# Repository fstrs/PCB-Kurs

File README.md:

# FHDO-PCB

Felix Strauß

Repository for FH Dortmund - Choiceduty-Module 4th Semster

We will design our own Bluetooth Speaker

- `/Code` -> Programmierungsdateien  
- `/Datenblätter` -> Datenblätter für Verwendete ICs und andere Komponenten  
- `/Dokumentation` -> Vorträge, Dokumentation der Projektarbeit  
- `/PCB` -> Dateien zum PCB-Design  

The full Documentation of the Project can be found at [Ausarbeitung.pdf](https://github.com/fstrs/PCB-Kurs/blob/main/Dokumentation/Ausarbeitung.pdf "Dokumentation/Ausarbeitung.pdf")

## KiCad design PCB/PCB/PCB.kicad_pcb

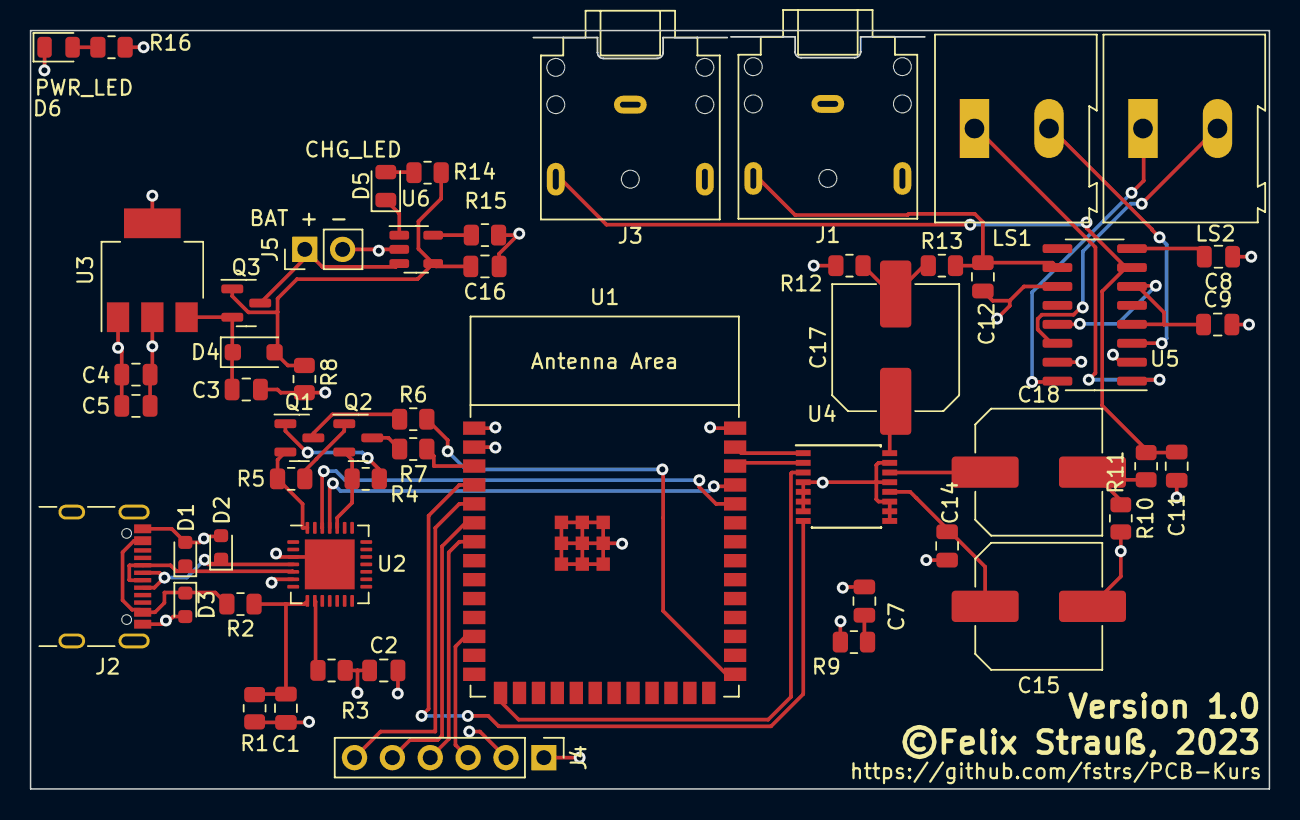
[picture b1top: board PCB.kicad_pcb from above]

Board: 4 copper layers, 83.1 x 50.8 mm, 53 parts (0 on the bottom side), 46 nets.

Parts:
C1, C5: 1u; C_0805_2012Metric
C2, C3, C4: 10u; C_0805_2012Metric
C7, C9, C16: 10µF; C_0805_2012Metric
C8, C14: 100nF; C_0805_2012Metric
C11, C12: 10nF; C_0805_2012Metric
C15, C17, C18: 47µF; C_Elec_8x10.2
D1, D2, D3: D_TVS; D_0603_1608Metric
D4: SS34FA; D_SOD-123F
D5: CHG_LED; LED_0805_2012Metric
D6: PWR_LED; LED_0805_2012Metric
J1: AudioJack Right; Jack_3.5mm_CUI_SJ1-3523N_Horizontal
J2: USB_C_Receptacle_USB2.0; USB_C_Receptacle_GCT_USB4105-xx-A_16P_TopMnt_Horizontal
J3: AudioJack Left; Jack_3.5mm_CUI_SJ1-3523N_Horizontal
J4: 6PIN DISPLAY CONNECTOR; PinHeader_1x06_P2.54mm_Vertical
J5: CONN BAT; PinHeader_1x02_P2.54mm_Vertical
LS1: Speaker Left; TerminalBlock_Altech_AK300-2_P5.00mm
LS2: Speaker Right; TerminalBlock_Altech_AK300-2_P5.00mm
Q1, Q2: BC817; SOT-23
Q3: BSS84; SOT-23
R1: 47K; R_0805_2012Metric
R2: 22K; R_0805_2012Metric
R3, R6, R7: 1K; R_0805_2012Metric
R4, R5, R8, R16: 10K; R_0805_2012Metric
R9: 1; R_0805_2012Metric
R10, R12: 220; R_0805_2012Metric
R11, R13: 100; R_0805_2012Metric
R14: 470; R_0805_2012Metric
R15: 2K; R_0805_2012Metric
U1: ESP32-S3-WROOM-1
U2: CP2102N-Axx-xQFN28; QFN-28-1EP_5x5mm_P0.5mm_EP3.35x3.35mm
U3: NCP1117-3.3_SOT223; SOT-223-3_TabPin2
U4: UDA1334ATS; SSOP-16_4.4x5.2mm_P0.65mm
U5: PAM8403D; SOP-16_3.9x9.9mm_P1.27mm
U6: MCP73831-3-OT; SOT-23-5

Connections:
+3.3V: C2.1, C4.1, C5.1, C9.2, J4.2, R3.1, R9.1, R16.2, U1.2 (3V3), U2.6 (VDD), U2.7 (VREGIN), U3.2 (VO)
+BATT: J5.1, Q3.3 (D), U6.3 (V_{BAT})
/EN: R7.2, U1.3 (EN)
/GPIO0: R6.2, U1.27 (GPIO0/BOOT)
/rxd: U1.36 (U0RXD/GPIO44/CLK_OUT2), U2.26 (TXD)
/txd: U1.37 (U0TXD/GPIO43/CLK_OUT1), U2.25 (RXD)
GND: C1.1, C2.2, C3.2, C4.2, C5.2, C7.1, C8.1, C11.2, C12.1, C14.2, C15.2, C16.2, D1.2 (A2), D2.2 (A2), D3.2 (A2), D6.1 (K), J1.S, J2.A1 (GND), J2.A12 (GND), J2.B1 (GND), J2.B12 (GND), J2.S1 (SHIELD), J3.S, J4.1, J5.2, R1.2, R8.2, R10.2, R12.1, R15.2, U1.1 (GND), U1.40 (GND), U1.41 (GND), U2.3 (GND), U2.29 (GND), U3.1 (GND), U4.4 (VDDD), U4.5 (VSSD), U4.6 (SYSCLK/PLL1), U4.7 (SFOR1), U4.9 (DEEM/CLKOUT), U4.10 (PLL0), U4.11 (SFOR0), U4.13 (VDDA), U4.15 (VSSA), U5.2 (PGND), U5.11 (GND), U5.15 (PGND), U6.2 (V_{SS})
unnamed: C7.2, R9.2
unnamed: C17.2, R12.2, R13.1
unnamed: C18.2, R10.1, R11.1
unnamed: D1.1 (A1), J2.A7 (D-), J2.B7 (D-), U2.5 (D-)
unnamed: D2.1 (A1), J2.A6 (D+), J2.B6 (D+), U2.4 (D+)
unnamed: D3.1 (A1), J2.A4 (VBUS), J2.A9 (VBUS), J2.B4 (VBUS), J2.B9 (VBUS), R2.2
unnamed: C3.1, D4.1 (K), Q3.2 (S), U3.3 (VI)
unnamed: D5.2 (A), R14.2
unnamed: D5.1 (K), U6.1 (STAT)
unnamed: D6.2 (A), R16.1
unnamed: J4.3, U1.12 (GPIO8/TOUCH8/ADC1_CH7/SUBSPICS1)
unnamed: J4.4, U1.7 (GPIO7/TOUCH7/ADC1_CH6)
unnamed: J4.5, U1.6 (GPIO6/TOUCH6/ADC1_CH5)
unnamed: J4.6, U1.5 (GPIO5/TOUCH5/ADC1_CH4)
unnamed: Q1.1 (B), R4.2
unnamed: Q1.3 (C), R6.1
unnamed: Q1.2 (E), R5.1, U2.28 (~DTR)
unnamed: Q2.1 (B), R5.2
unnamed: Q2.3 (C), R7.1
unnamed: Q2.2 (E), R4.1, U2.24 (~RTS)
unnamed: U1.39 (GPIO1/TOUCH1/ADC1_CH0), U4.1 (BCK)
unnamed: U1.38 (GPIO2/TOUCH2/ADC1_CH1), U4.2 (WS)
unnamed: U1.15 (GPIO3/TOUCH3/ADC1_CH2), U4.3 (DATAI)
unnamed: U1.4 (GPIO4/TOUCH4/ADC1_CH3), U4.8 (MUTE)
unnamed: C1.2, R1.1, R2.1, U2.8 (VBUS)
unnamed: R3.2, U2.9 (~RST)
unnamed: C18.1, U4.14 (VOUTL)
unnamed: C17.1, U4.16 (VOUTR)
unnamed: C14.1, C15.1, U4.12 (Vref(DAC))
unnamed: C11.1, J3.T, R11.2, U5.7 (INL)
unnamed: C12.2, J1.T, R13.2, U5.10 (INR)
unnamed: LS1.1, U5.1 (LOUT+)
unnamed: LS1.2, U5.3 (LOUT-)
unnamed: LS2.1, U5.16 (ROUT+)
unnamed: LS2.2, U5.14 (ROUT-)
unnamed: C9.1, U5.4 (PVDD), U5.6 (VDD), U5.13 (PVDD)
unnamed: C8.2, U5.8 (VREF)
unnamed: R15.1, U6.5 (PROG)
VBUS: C16.1, D4.2 (A), Q3.1 (G), R8.1, R14.1, U6.4 (V_{DD})

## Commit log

2023-03-29 Datasheets
2023-03-29 architecture Layout first edit
2023-04-19 Testcommit
2023-04-19 renamed folder /Datenblätter
2023-04-19 updated Architekturdiagramm
2023-04-21 added ESP32 Datasheet
2023-04-26 first PCB draft
2023-05-03 first draft
2023-05-03 added DAC and AMP
2023-05-03 added Audio Processing
2023-05-03 edit Vorlesung
2023-05-17 Organised
2023-05-18 PCB Verion 1.0
2023-05-24 Removed Errors
2023-05-31 PCB finished
2023-05-31 added PCB print
2023-09-11 finished Documentation
2023-09-11 added Documentation link

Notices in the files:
PCB/PCB/PCB.kicad_pcb:
©Felix Strauß, 2023
